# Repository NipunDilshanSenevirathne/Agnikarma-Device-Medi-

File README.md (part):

# Agni Karma Portable

**Five-preset thermal-applicator engineering project — P3R1, release 0.5.0.**

The intended product is a portable, battery-powered applicator with **50 / 100 / 150 / 200 / 250 degrees Celsius**, one interchangeable brass tip at a time, simple controls and a dedicated COOL button. This repository contains the current prototype software, electrical definition, routed controller carrier, mechanical source, engineering calculations and verification records.

**Current status:** the implemented design is a guarded modular bench prototype. It has not been manufactured, run on physical Pico boards or validated for patient use. The compact handheld housing, complete heated cartridge, qualified battery/charger and medical release are unfinished. The [build-completeness assessment](BUILD_COMPLETENESS.md) identifies those gaps. This README explains both the supplied implementation and the work needed to develop it further.

*AI-generated appearance illustration of the intended handheld product. Its housing is not the enclosure supplied for the current modular electronics. Rendered screens and wires are illustrations, not measured equipment or wiring instructions.*

## Contents

- [Project scope and current status](#project-scope-and-current-status)
- [Start here and document authority](#start-here-and-document-authority)
- [Functional requirements and user controls](#functional-requirements-and-user-controls)
- [System architecture and illustrations](#system-architecture-and-illustrations)
- [Repository layout and deliverables](#repository-layout-and-deliverables)
- [Parts list and procurement](#parts-list-and-procurement)
- [Power distribution and electrical boundaries](#power-distribution-and-electrical-boundaries)
- [Heater switching and relay circuit](#heater-switching-and-relay-circuit)
- [Controls and physical interlocks](#controls-and-physical-interlocks)
- [Temperature sensing and analog monitoring](#temperature-sensing-and-analog-monitoring)
- [Pico GPIO and physical header map](#pico-gpio-and-physical-header-map)
- [Routed PCB and fabrication files](#routed-pcb-and-fabrication-files)
- [Mechanical assembly and brass contact ends](#mechanical-assembly-and-brass-contact-ends)
- [Heater material and power calculations](#heater-material-and-power-calculations)
- [Battery charging and COOL behaviour](#battery-charging-and-cool-behaviour)
- [Computer setup and source verification](#computer-setup-and-source-verification)
- [Firmware deployment and commissioning records](#firmware-deployment-and-commissioning-records)
- [Operating sequence and software states](#operating-sequence-and-software-states)
- [Firmware limits protocol and failure boundaries](#firmware-limits-protocol-and-failure-boundaries)
- [Bench build sequence and inspection gates](#bench-build-sequence-and-inspection-gates)
- [Calibration and measurement records](#calibration-and-measurement-records)
- [Verification results and evidence limits](#verification-results-and-evidence-limits)
- [Troubleshooting and recovery](#troubleshooting-and-recovery)
- [Reproducing diagrams CAD and calculations](#reproducing-diagrams-cad-and-calculations)
- [Packaging GitHub and repository maintenance](#packaging-github-and-repository-maintenance)
- [Remaining engineering and medical release work](#remaining-engineering-and-medical-release-work)
- [Research sources and image provenance](#research-sources-and-image-provenance)
- [Appendix full system bill of materials](#appendix-full-system-bill-of-materials)
- [Appendix complete carrier connector table](#appendix-complete-carrier-connector-table)
- [Appendix all component terminal connections](#appendix-all-component-terminal-connections)

## Project scope and current status

The project has three distinct physical subjects: the **controller assembly**, the **external guarded power/sensor fixture**, and the **future interchangeable heated cartridge**. Understanding their boundaries is necessary before ordering or connecting parts.

| Subject | Supplied in this release | Development still required |
|---|---|---|
| Control software | Actual MicroPython applications for MAIN and SUPERVISOR, drivers, provisioning, host tests and simulation | Target execution, measured timing, hardware fault tests and software release validation |
| Electrical definition | Named components, values, full terminal connections, GPIO map and full-system schematic | Independent circuit/package review and physical electrical, thermal and fault measurements |
| Controller PCB | Routed 160 x 100 mm two-layer low-current carrier, matched schematic, local libraries and native reports | Independent CAM and purchased-part fit review, fabrication, assembly and continuity testing |
| Fabrication candidates | Six Gerber layers, separate plated/non-plated drills, maps and job file | Fabricator/assembler review and approval before ordering |
| Controller enclosure | Parametric 180 x 120 x 65 mm base, lid, mounts and harness cover; compiled meshes | Exact switch/display adapter fit, material, strength, wiring clearance and thermal testing |
| Brass contact ends | Five nominal shape models; T01/T02 electrical identity codes | Controlled material/process/tolerances and complete cartridge construction; T03–T05 software support |
| Heating cartridge | Functional supplier specification and resistance-wire calculations | Actual heater, ceramic, insulation, joints, dual sensors, lock, seals and supplier/finished-device testing |
| Portable power | Protected 2S architecture and monitoring circuits | Exact pack and matching charger, charging lockout, protection coordination, transport and heat-soak tests |
| Cooling | Physical relay-coil interruption and latched software cooling/inhibition | Measured cooldown and safe-handling criteria; active cooling if separately designed |
| Medical release | Risk, traceability, testing and handover documents | Intended use/market decisions, quality work, electrical/EMC, biological, reprocessing, usability and clinical/regulatory evidence |

The carrier is a **Pico breakout board**. It does not contain the external gate driver, power MOSFET, relay, branch resistors, sensor boards, ADC protection or battery charger. A populated carrier alone is not the complete controller circuit.

The AI illustrations, native CAD renders, calculation worksheets, host tests and physical-test forms have different evidentiary roles. A blank test form is a plan; a native rendering is a geometric view; a passing host test is a software result. None is a photograph or physical performance measurement.

## Start here and document authority

Use this README as the overview and detailed navigation guide. When making a connection, use the machine-readable terminal records and the applicable manufacturer drawing together.

| File | What it defines |
|---|---|
| [START_HERE.md](START_HERE.md) | Entry points and current project scope |
| [BUILD_GUIDE.md](BUILD_GUIDE.md) | Integrated prototype assembly sequence |
| [hardware/design.json](hardware/design.json) | Component references, terminal names, nets and notes |
| [hardware/BOM.csv](hardware/BOM.csv) | Full system component list, values and assembly notes |
| [hardware/component_connections.csv](hardware/component_connections.csv) | Every defined component terminal and its net |
| [hardware/pinmap.csv](hardware/pinmap.csv) | Pico GPIO number versus physical header pin |
| [hardware/net_schedule.csv](hardware/net_schedule.csv) | All terminals joined by each net name |
| [hardware/carrier_connectors.csv](hardware/carrier_connectors.csv) | Breakout connector pin versus Pico physical pin |
| [hardware/carrier_BOM.csv](hardware/carrier_BOM.csv) | Carrier board, sockets, headers, inlet and proposed fasteners |
| [hardware/procurement_checklist.csv](hardware/procurement_checklist.csv) | Purchased revisions, supplier decisions and evidence still needed |
| [AUDIT_REPORT.md](AUDIT_REPORT.md) | Corrected findings and current limitations |
| [BUILD_COMPLETENESS.md](BUILD_COMPLETENESS.md) | Remaining manufacturing and medical release gates |
| [docs/engineering-handover.md](docs/engineering-handover.md) | Instructions for an engineer, cartridge supplier and subsequent development |

In the connection records, identical non-NC net names mean electrical continuity. Names beginning with `NC_` identify terminals that remain unconnected. Do not join all NC terminals into a common circuit.

A module terminal such as `VIN`, `SDI`, `COM` or `COIL_A` is a functional terminal name. It does not automatically specify a numbered leg on the internal IC or relay package. Identify real package legs from the exact purchased part's manufacturer drawing. GPIO `GP21`, Pico physical pin `27` and carrier connector numbering are three different labels for related locations; do not interchange the numbers.

## Functional requirements and user controls

| Function | Current behaviour |
|---|---|
| Temperature selection | Five momentary buttons: **50, 100, 150, 200 and 250 C**; 300 C is not selectable |
| Startup | MAIN defaults to a 50 C target but remains locked with output inhibited |
| Tip connection | One positively locked, identified tip at a time; T01/T02 codes are recognized |
| ARM | A deliberate release followed by a new press, while HEAT is released, requests arming when checks are healthy |
| HEAT | Must be held to request heater energy; releasing it removes the output request |
| COOL | Interrupts the relay-coil supply through one physical switch pole and sends a logic request through the other |
| After COOL | Output stays inhibited; releasing COOL does not restart heating; valid conditions and a new ARM sequence are required |
| Setting change/fault | Disarms the controller; healthy readings alone do not restore heating |
| Docked condition | Physical coil interruption and logic inhibition |
| Tip removal/unlock | Opens the intended physical interlock and removes the logic permit |
| Display | MAIN shows state, selected setpoint, measured tip temperature, pack voltage and fault/status text |
| Temperature disagreement | Each controller checks its local sensor against the peer temperature |
| Communications loss | Stale UART or missing health pulses withdraw the software permit |

The five numbers are the available **setpoints**. The firmware also displays actual temperature and fault information. The illustrated five-value selection screen is not a literal capture of the running display.

Selection is shared through individual resistor branches to both boards. Firmware rejects a multiple-key condition. Press one selection button deliberately and allow both controllers to agree before arming; the operating procedure uses a press of at least 200 ms. This is a bench interaction procedure, not a clinical treatment protocol.

## System architecture and illustrations

MAIN reads its Pt1000 sensor, user inputs and monitoring circuits, runs the bounded temperature loop, updates the OLED and drives the PWM gate-driver input. SUPERVISOR reads a separate Pt1000 channel and its own monitoring/input branches, checks MAIN's status and controls the relay-coil transistor. MAIN also requires a healthy supervisor permit before delivering PWM.

The two controllers exchange CRC-protected UART frames and separate toggling health-pulse signals. A pulse is emitted after a completed acquisition/control/transmit iteration. Two boards improve monitoring options, but common software, runtime, supply, switches and ground remain common-cause failure paths requiring assessment.

```mermaid
flowchart LR
    P[Protected 2S pack or guarded bench source] --> F[F1 fused supply]
    F --> B[Pololu regulated 5 V logic supply]
    B --> M[MAIN Pico and local measurements]
    B --> S[SUPERVISOR Pico and local measurements]
    F --> K[K1 normally-open heater contact]
    K --> H[Guarded load or future insulated cartridge]
    H --> Q[Q1 PWM return switch]
    Q --> G[Power return]
    M --> D[TC4420 gate driver]
    D --> Q
    S --> C[Relay-coil transistor]
    I[Physical COOL / dock / lock chain] --> C
    M <--> S
```

The Mermaid drawing is functional. Use the terminal records and detailed drawings for actual contact/driver wiring.

*AI-generated bench-equipment illustration constrained to the specified equipment families. Individual leads and package geometry are approximate. The current native PCB and enclosure views below show supplied CAD; neither image proves assembly or wiring.*

## Repository layout and deliverables

```text
agni karma/
  README.md                    Detailed project guide
  START_HERE.md                Entry points
  BUILD_GUIDE.md               Integrated assembly sequence
  BUILD_COMPLETENESS.md        Open release gates
  AUDIT_REPORT.md              Source corrections and current findings
  SOURCE_MANIFEST.json         SHA-256 inventory of delivered source files
  firmware/
    app.py                     RP2040 hardware adapter and loop
    core.py                    Controllers, samples, fault logic and link protocol
    config.py                  Pins, five presets and provisional bench limits
    provision.py               Configuration validation
    provision.example.json     Disabled example commissioning record
    boot_main.py               MAIN role entry point
    boot_supervisor.py         SUPERVISOR role entry point
    drivers/                   MAX31865 and OLED drivers
  hardware/
    BOM.csv                    Full system BOM
    design.json                Machine-readable electrical definition
    component_connections.csv  Component-terminal-to-net data
    pinmap.csv                 GPIO and Pico physical header map
    net_schedule.csv           Connections grouped by net
    carrier_BOM.csv            Carrier assembly items
    carrier_connectors.csv     All four breakout headers
    procurement_checklist.csv  Supplier and qualification decisions
    calculations/              Power, drive, divider and resistance-wire worksheets
    kicad/                     Native projects, schematics, board and local libraries
    drawings/                  Native schematic/layer PDFs and exported netlist
    fabrication/P3R1/          Candidate Gerbers, drills, maps and instructions
  mechanical/
    bench_enclosure.scad       Controller base, lid, mounts and harness cover
    tips.scad                  Five nominal brass contact-end shapes
    assembly_parameters.json   Dimensions, locations and fit boundaries
    exports/                   Eight STL meshes and board-only STEP
  docs/
    images/                    AI illustrations, native renders and engineering drawings
    records/                   Actual check results and blank measurement forms
    ...                        Electrical, firmware, mechanical, test and handover guides
  tests/                       Host/integration/design/tooling checks
  tools/                       Verification, deployment, generation and packaging
  .github/                     CI workflow and issue/PR templates
```

`build/`, Python caches, local provisioning, editor caches and release ZIPs are generated/local material. They are excluded from the distributable source package. The cleaned project folder contains the current files and manifest; release archives are stored separately.

## Parts list and procurement

The full system contains **78 defined component references**. A reference is a design item, not proof that an exact supplier SKU, purchased revision or final cartridge has been qualified. Full values and notes appear in the BOM appendix below.

| Subsystem | Defined part or specification | Procurement consideration |
|---|---|---|
| MAIN/SUPERVISOR | Two original Raspberry Pi Pico RP2040 boards | Confirm purchased revision, header orientation and target runtime |
| RTD interfaces | Two Adafruit **3648** Pt1000 MAX31865 breakouts | 4.3 kohm reference version; a Pt100 board is not equivalent |
| Temperature elements | Two separate four-wire Pt1000 assemblies, alpha 0.00385 family | Actual package, leads, retention and insulation remain supplier work |
| Logic regulator | Pololu **2858 / D24V22F5** | Regulated 5 V to VSYS; review input/thermal conditions |
| Gate driver | **TC4420CPA**, non-inverting, PDIP-8 | TC4429 inverting variant is not a direct substitute |
| PWM switch | Infineon **IRLZ44NPBF**, TO-220 | Verify gate drive, dissipation, mounting and live drain tab |
| Heater relay | Omron **G5LE-1-DC5** | Normally-open contact; not a certified redundant safety relay |
| Relay transistor | onsemi **PN2222ABU**, TO-92 | Exact package pinout matters; similarly named variants can differ |
| Flyback diode | **1N4007** | Polarity across coil; suppression affects release time |
| Display | Adafruit **326**, STEMMA QT auto-reset SSD1306 revision | I2C mode/address and actual adapter fit must be checked |
| Commissioning load | **2.2 ohm, at least 100 W chassis resistor**, on its specified heat sink | Continuous rating depends on mounting/heat sink; not a medical tip |
| Initial fuse proposal | **5 A**, with suitable DC-rated holder | Final interrupt rating and curve/wire/pack coordination remain open |
| Controls | Five NO preset buttons, ARM, HEAT, DPDT COOL, two-pole dock/lock switches | Exact parts/contact ratings and fit need selection |
| Portable source | Protected **2S** battery pack and matched charger | Exact models, charge lockout and system qualification are open |

Carrier-only components and proposed fasteners are separately defined:

| Reference | Quantity | Specification | Use or review |
|---|---|---|---|
| `PCB_CARRIER` | 1 | AGNI P3R1; 160 x 100 mm; 2-layer FR4; nominal 1.6 mm; 35 um copper; mask both sides; top silkscreen | Fabrication candidate only; independent CAM and physical footprint review before order |
| `A1/A2 sockets` | 4 | 1x20 female socket strip; 2.54 mm pitch; 0.64 mm square-pin compatible; straight through-hole; 1.0 mm PCB drill | Two strips per Pico; choose matched stack height; verify orientation and engagement |
| `J1/J2/J3/J4` | 4 | 1x20 straight male header; 2.54 mm pitch; 0.64 mm square posts; 1.0 mm drill | Low-current external breakouts; external 1k branches and all other circuits still required |
| `J5` | 1 | Phoenix Contact 1715721 MKDS 1.5/2-5.08; 2-position; 5.08 mm pitch; 1.3 mm drill | Pin 1 GND; pin 2 regulated 5 V only; confirm actual footprint and torque against current supplier drawing |
| `Carrier screws` | 4 | M3 x 6 pan head; insulating washers as needed | Fit model pilot posts; check protrusion and engagement |
| `Lid screws` | 4 | M3 x 10 pan head | Fit model pilot posts; qualify repeated use |
| `Clamp screws` | 2 | M3 x 10 pan head with washers | Check cable retention; insulating grommet required |

Do not add carrier sockets/headers to the full system twice when preparing a purchase order. The two Pico modules are already system items; socket strips support those modules. Module-internal ICs/passives remain manufacturer-controlled components rather than a guessed replacement circuit in this repository.

Record supplier, exact part revision, evidence identifier and substitutions in [procurement_checklist.csv](hardware/procurement_checklist.csv). Wire gauge, high-current connector, final fuse, battery, charger, precise sensor package, switches and complete cartridge must be resolved before treating procurement as finished. No current prices, supplier quotations or total product cost are established here.

## Power distribution and electrical boundaries

The nominal heating branch and regulated logic branch share the defined return but have different current paths:

```text
Source positive -> F1 -> PACK_FUSED -> K1 COM
K1 NO -> HEAT_PLUS -> guarded load/heater -> HEAT_MINUS -> Q1 drain
Q1 source -> dedicated power return -> source negative

PACK_FUSED -> Pololu VIN
Pololu VOUT 5 V -> carrier J5 pin 2 -> Pico VSYS, driver and coil circuit
Power/logic GND -> carrier J5 pin 1 and the defined circuit return

MAIN 3V3_OUT -> MAIN RTD interface and MAIN measurement pull-ups
SUP  3V3_OUT -> SUP  RTD interface and SUP  measurement pull-ups
```

The two Pico **3V3_OUT** pins are separate regulator outputs. Keep `3V3_MAIN` and `3V3_SUP` separate. `5V` is regulated logic power; `PACK_FUSED` is the fused battery/bench input. Never substitute one for the other at the Pico, GPIO, ADC or carrier inlet.

Do not route heater current through the carrier headers, sensor-module ground leads or a solderless breadboard. Use mechanically retained, appropriately rated power terminals/harnesses and a controlled return arrangement. Review layout, conductor/insulation ratings, loop area, supply transients and grounding against measured currents. A nominal fuse value alone does not settle these questions.

Keep USB disconnected during powered heater tests unless the combined USB/bench/battery supply and grounding arrangement has been reviewed. USB can introduce another return or source path; it is not medical isolation. The passive carrier has no reverse-polarity protection.

Start commissioning with an instrumented current-limited bench supply and disconnected heater. A portable pack is a later integration step; it is not automatically qualified by using a protected cell assembly.

## Heater switching and relay circuit

[Detailed terminal wiring PNG](docs/images/terminal-wiring.png) · [editable terminal wiring SVG](docs/images/terminal-wiring.svg) · [full-system schematic PDF](hardware/drawings/module-system-schematic.pdf)

### Main PWM path

MAIN `GP21` drives `PWM_INPUT`. U1 is the non-inverting TC4420CPA powered from regulated 5 V. Its duplicated output pins join `DRIVE`; the 10 ohm resistor connects DRIVE to Q1 gate. Q1 switches the heater return at the configured 1 kHz PWM frequency.

| Part / terminal | Defined connection |
|---|---|
| U1 pins 1 and 8 | Regulated `5V` |
| U1 pin 2 | `PWM_INPUT` from MAIN GP21 |
| U1 pin 3 | Unconnected (`NC_U1_3`) |
| U1 pins 4 and 5 | `GND` |
| U1 pins 6 and 7 | Joined as `DRIVE` |
| R1, 10 ohm | DRIVE to Q1 gate (`MOS_GATE`) |
| R2, 100k | Q1 gate to source/GND |
| R3, 100k | Driver input to GND |
| C1, 100 nF / 25 V X7R | Driver 5 V bypass to GND |
| C2, 1 uF / 25 V X7R | Driver 5 V bypass to GND |
| C3, 100 uF / 16 V low ESR | Positive to 5 V, negative to GND |
| Q1 pin 1 | Gate |
| Q1 pin 2 and tab | Drain / `HEAT_MINUS` |
| Q1 pin 3 | Source / power GND |

The package/duplicate-pin reference is the [Microchip TC4420/TC4429 datasheet](https://ww1.microchip.com/downloads/en/DeviceDoc/21419D.pdf). Keep bypass loops short at the driver. The Q1 tab is electrically live drain, so a heat sink, screw or chassis contact must not create an unintended connection. Actual switching waveform, gate behaviour, losses and surface temperatures must be measured.

### Supervisor relay path

K1 COM receives `PACK_FUSED`; its normally-open contact supplies `HEAT_PLUS`. Its unused normally-closed contact stays unconnected. The coil circuit is separate from those power contacts.

```text
5V -> COOL pole A COM/NC -> dock pole A COM/NC
   -> locked-tip pole A COM/NO -> K1 COIL_A
K1 COIL_B -> Q2 collector
Q2 emitter -> GND
SUPERVISOR GP21 -> R4 330 ohm -> Q2 base
Q2 base -> R5 100k -> GND
D1 cathode -> COIL_A; D1 anode -> COIL_B
```

For the specified PN2222ABU record, terminals are **1 emitter, 2 base, 3 collector**. Verify the actual manufacturer's drawing and package before soldering. The repository uses Omron coil/COM/NO functional names; identify the real relay legs from its exact package drawing rather than assuming those names are pin numbers.

Opening COOL, docking or unlocking/removing the cartridge interrupts the intended coil chain. A welded relay contact or shorted MOSFET is a separate fault scenario; the circuit has not been certified to tolerate those faults. A flyback diode protects the coil switch but changes release timing. Measure relay release and resulting energy instead of treating the software timeout as the physical stop time.

## Controls and physical interlocks

Each shared logic switch connects a bus to GND when active. Each controller reaches that bus through its **own 1k branch resistor**, using its own internal input pull-up. This shares the switch action without joining the two 3V3 regulator outputs.

For an ordinary preset, the path is `MAIN GPIO -> MAIN 1k -> switch bus`, `SUP GPIO -> SUP 1k -> same bus`, then the NO switch to GND. ARM and HEAT use the same branching principle. The full terminal appendix contains their actual reference/net names.

| Interlock | Physical pole A | Logic pole B | Meaning when actuated |
|---|---|---|---|
| COOL | COM to NC is in the coil supply path | COM GND to NO `COOL_LOGIC` | Coil supply opens and both controllers read COOL active |
| Dock | COM to NC is in the coil supply path | COM GND to NO `DOCK_LOGIC` | Coil supply opens and both controllers read docked |
| Tip lock | COM to NO is in the coil supply path | COM GND to NO `TIP_PRESENT` | Positive locking must close the intended contacts; unlocked state inhibits |

Pole A and pole B must be electrically separate. Do not connect the 5 V coil chain to a GPIO logic bus. A single-pole replacement for the specified DPDT COOL function is insufficient. Confirm physical actuation/sequence and contact ratings against coil current and the real mechanism.

The logic inputs are active-low. The tip-present contact closes only when a cartridge is positively locked; an operator holding a loose part near a connector is not an equivalent mechanical condition. Broken, stuck, shorted and bouncing wires/switches still require controlled physical fault tests.

## Temperature sensing and analog monitoring

[Editable sensor-wiring SVG](docs/images/sensor-wiring.svg)

### Two separate Pt1000 channels

Each controller has its own Adafruit 3648 MAX31865 interface, its own Pt1000 element and its own 3V3 regulator output. The configured reference is nominally **4300 ohm**, and the nominal RTD resistance is **1000 ohm at 0 C**. The firmware uses continuous conversion, four-wire configuration and 50 Hz rejection.

| Interface terminal | Controller / sensor connection |
|---|---|
| VIN | That controller's own 3V3 output |
| GND | Defined GND |
| SCK | Local GP6 |
| SDI | Local GP7 MOSI |
| SDO | Local GP4 MISO |
| CS | Local GP5 |
| F+ | Force lead at sensor element end A |
| RTD+ | Separate sense lead at the same element end A |
| RTD- | Sense lead at element end B |
| F- | Separate force lead at the same element end B |
| 3Vo | Unused output; leave unconnected |

Identify element-end pairs from the actual sensor documentation and measurements, not wire colour alone. A two-wire element with arbitrary added wires is not automatically the qualified four-wire cartridge assembly specified here. Keep the supplied four-wire jumper arrangement appropriate to the actual module; verify with the [manufacturer terminal guide](https://learn.adafruit.com/adafruit-max31865-rtd-pt100-amplifier/pinouts).

SPI0 is configured at **500 kHz, polarity 0, phase 1**. MAIN and SUPERVISOR do not share the same SPI sensor module. Sensor-to-working-face gradients, response lag, attachment integrity and electrical insulation remain cartridge verification tasks.

### Pack voltage

Each controller has its own chain: `PACK_FUSED -> 100k -> divider node -> 39k -> GND`. A separate 1k resistor connects the divider node to that controller's GP26 ADC. The ADC node has 10 nF to GND, an upper BAT54 clamp with anode at ADC/cathode at its own 3V3 rail, and a lower BAT54 clamp with anode at GND/cathode at ADC.

The firmware's ideal conversion is:

```text
pack_v = adc_u16 / 65535 * 3.3 * (139 / 39) * battery_scale
```

At an 8.5 V input, the ideal divider output is about 2.385 V; the worksheet's 1% worst-case resistor mismatch gives about 2.419 V. Actual ADC/reference behaviour, filtering, clamp leakage and unpowered backfeeding need measurement. Do not connect pack voltage directly to a Pico ADC or treat the clamps as complete pack protection.

### Pack temperature

Each controller has a 10k pull-up from its own 3V3 rail to GP27 and an insulated **10k at 25 C, B3950 NTC** from that node to GND. The software converts the divider ratio using the configured beta approximation. The two sensors need appropriate thermal attachment to the pack and independent wiring; electrical readings alone do not prove good thermal coupling.

### Tip identity

Each controller has a 10k pull-up from its own 3V3 rail to GP28 and its own cartridge code resistor to GND:

| Tip | Code resistor per channel | Nominal ADC ratio | Current firmware |
|---|---|---|---|
| T01 | 10k | 0.5000 | Recognized |
| T02 | 16k | 0.6154 | Recognized |
| T03/T04/T05 | No released code | No supported ratio | Not supported |

The ratio acceptance tolerance is nominally +/-0.025. The two channels use separate pull-up/code circuits. A resistor code does not establish authenticity, sterility or a valid calibration. The current UART frame does not carry the tip ID for a separate peer-ID comparison; each controller checks its own recognized code. Additional identity/calibration features require a reviewed implementation.

### Display

Use the specified Adafruit 326 **STEMMA QT auto-reset** revision. The defined wiring is VIN to `3V3_MAIN`, GND to GND, SDA to MAIN GP2 and SCL to MAIN GP3. MAIN uses I2C1 at 400 kHz. The older reset-dependent display revision needs a changed circuit/firmware and is not covered by this wiring.

Provision the actual address as decimal **60 (0x3C)** or **61 (0x3D)**. A missing display prevents normal MAIN provisioning. The display update interval is at least 250 ms in the application; displayed state is not an independent temperature measurement or clinical READY signal.

## Pico GPIO and physical header map

Both controllers use the same GPIO roles except that the display belongs to MAIN and the GP21 outputs perform different functions. The table is generated from [pinmap.csv](hardware/pinmap.csv); its GPIO column is not a connector-pin number.

| GPIO | Pico physical pin | MAIN net | SUPERVISOR net |
|---|---|---|---|
| `GP0` | 1 | `MAIN_TX` | `SUP_TX` |
| `GP1` | 2 | `MAIN_RX` | `SUP_RX` |
| `GP2` | 4 | `OLED_SDA` | `Unassigned` |
| `GP3` | 5 | `OLED_SCL` | `Unassigned` |
| `GP4` | 6 | `MAIN_MISO` | `SUP_MISO` |
| `GP5` | 7 | `MAIN_CS` | `SUP_CS` |
| `GP6` | 9 | `MAIN_SCK` | `SUP_SCK` |
| `GP7` | 10 | `MAIN_MOSI` | `SUP_MOSI` |
| `GP8` | 11 | `MAIN_KEY_50` | `SUP_KEY_50` |
| `GP9` | 12 | `MAIN_KEY_100` | `SUP_KEY_100` |
| `GP10` | 14 | `MAIN_KEY_150` | `SUP_KEY_150` |
| `GP11` | 15 | `MAIN_KEY_200` | `SUP_KEY_200` |
| `GP12` | 16 | `MAIN_KEY_250` | `SUP_KEY_250` |
| `GP14` | 19 | `MAIN_KEY_COOL` | `SUP_KEY_COOL` |
| `GP15` | 20 | `MAIN_KEY_HEAT` | `SUP_KEY_HEAT` |
| `GP16` | 21 | `MAIN_KEY_ARM` | `SUP_KEY_ARM` |
| `GP17` | 22 | `MAIN_KEY_DOCK` | `SUP_KEY_DOCK` |
| `GP18` | 24 | `MAIN_KEY_TIP` | `SUP_KEY_TIP` |
| `GP19` | 25 | `MAIN_PULSE_IN` | `SUP_PULSE_IN` |
| `GP20` | 26 | `MAIN_PULSE_OUT` | `SUP_PULSE_OUT` |
| `GP21` | 27 | `PWM_INPUT` | `SUP_RELAY_OUTPUT` |
| `GP26` | 31 | `MAIN_PACK_ADC` | `SUP_PACK_ADC` |
| `GP27` | 32 | `MAIN_NTC_ADC` | `SUP_NTC_ADC` |
| `GP28` | 34 | `MAIN_ID_ADC` | `SUP_ID_ADC` |

Additional supply and ground connections on each Pico are:

| Physical Pico pin | Function in this assembly |
|---|---|
| 39 | VSYS from regulated 5 V |
| 36 | That Pico's own 3V3_OUT; keep the two boards' outputs separate |
| 3, 8, 13, 18, 23, 28, 33, 38 | GND on the carrier |
| 17 / GP13 | Unused in the five-preset design |
| 29 / GP22 | Reserved/spare in configuration; not assigned to an implemented external function |
| 30 / RUN | Unconnected on the carrier |
| 35 / ADC_VREF | Unconnected external breakout pad |
| 37 / 3V3_EN | Unconnected on the carrier |
| 40 / VBUS | Unconnected on the carrier; not a battery-power inlet |

SUPERVISOR GP2/GP3 have no display assignment in the supplied pin schedule. Unused Pico positions and corresponding breakout pads are isolated from one another rather than routed as arbitrary extra signals.

UART0 runs at **115200 baud**. MAIN TX goes through `R_LINK_M` 1k to SUP RX; SUP TX goes through `R_LINK_S` 1k to MAIN RX. MAIN GP20 health output goes through `R_PULSE_M` 1k to SUP GP19. SUP GP20 goes through `R_PULSE_S` 1k to MAIN GP19. The peer pulse inputs use pull-downs; the normal local outputs begin low.

## Routed PCB and fabrication files

*These are KiCad 10.0.8 raytraces of the actual supplied bare-board geometry. Component bodies are not fitted in these renders. They are neither AI board concepts nor photographs of manufactured hardware.*

### Board geometry and connector orientation

| Feature | Current definition |
|---|---|
| Board size | 160 x 100 mm |
| Board thickness | Nominal 1.6 mm |
| Copper layers | Two; proposed nominal 35 um copper, subject to fabricator agreement |
| Signal tracks | 0.35 mm |
| Logic supply/ground tracks | 0.60 mm; no heater-current capacity claim |
| Declared clearance | 0.20 mm |
| Declared copper-to-edge minimum | 0.50 mm |
| Pico row pitch | 2.54 mm longitudinal, 17.78 mm between rows |
| MAIN left header row | X=35 mm, top pad Y=20 mm |
| SUP left header row | X=105 mm, top pad Y=20 mm |
| Header drills | 1.0 mm |
| J5 terminal drills | 1.3 mm |
| Mounting holes | Four non-plated 3.2 mm holes at (5,5), (155,5), (5,95), (155,95) mm |

Coordinates are measured from the board's upper-left corner in the supplied CAD convention. The mounting pattern is also recorded in [assembly_parameters.json](mechanical/assembly_parameters.json).

J1 is MAIN's left breakout, J2 its right breakout, J3 SUP's left breakout and J4 its right breakout. **Each breakout strip is numbered from top to bottom 1–20.** On J1/J3, connector pin `j` corresponds to Pico physical pin `j`. On J2/J4, connector pin `j` corresponds to Pico physical pin `41-j`. Thus right breakout pin 1 corresponds to Pico physical pin 40; it is an isolated unused position, not MAIN/SUP TX.

J5 is a two-position **regulated logic-power inlet**: **pin 1 GND, pin 2 regulated 5 V**. The selected terminal is Phoenix Contact 1715721, MKDS 1.5/2-5.08. Verify the real purchased terminal and footprint before ordering. Never apply `PACK_FUSED` or heater current to J5.

The complete four-header map appears in the carrier appendix below. The native netlist tests compare it with the separate Pico pin schedule, including right-side reversal and isolated unused pads.

### Source and drawing files

| Item | File |
|---|---|
| Carrier project | [agni-controller-carrier.kicad_pro](hardware/kicad/agni-controller-carrier.kicad_pro) |
| Carrier schematic | [agni-controller-carrier.kicad_sch](hardware/kicad/agni-controller-carrier.kicad_sch) |
| Routed carrier board | [agni-controller-carrier.kicad_pcb](hardware/kicad/agni-controller-carrier.kicad_pcb) |
| Full-system schematic project | [agni-module-system.kicad_pro](hardware/kicad/agni-module-system.kicad_pro) |
| Full-system module/terminal schematic | [agni-module-system.kicad_sch](hardware/kicad/agni-module-system.kicad_sch) |
| Project symbol library | [AGNI.kicad_sym](hardware/kicad/AGNI.kicad_sym) |
| Library tables | [sym-lib-table](hardware/kicad/sym-lib-table), [fp-lib-table](hardware/kicad/fp-lib-table) |
| Carrier schematic PDF | [carrier-schematic.pdf](hardware/drawings/carrier-schematic.pdf) |
| Full-system schematic PDF | [module-system-schematic.pdf](hardware/drawings/module-system-schematic.pdf) |
| Copper/silk/outline PDF | [carrier-layers.pdf](hardware/drawings/carrier-layers.pdf) |
| Native layer plots | [top SVG](docs/images/carrier-top.svg), [bottom SVG](docs/images/carrier-bottom.svg), [combined routing SVG](docs/images/carrier-routing.svg) |
| Exported electrical netlist | [carrier-netlist.xml](hardware/drawings/carrier-netlist.xml) |
| Board-only mechanical model | [carrier-board-only.step](mechanical/exports/carrier-board-only.step) |

The `hardware/kicad/AGNI.pretty/` directory contains the project-local footprints. Keep it and both library tables with the project so references remain portable.

Both schematics use embedded/project-local **generic passive terminal symbols**. Native ERC verifies the represented connectivity and structure; it does not check real internal IC power/signal directions. The full-system schematic covers external circuits that are absent from the carrier PCB. A clean carrier DRC is not a safety test of the complete heater circuit.

### Candidate CAM outputs

Read [fabrication/P3R1/README.md](hardware/fabrication/P3R1/README.md) before sending files to a fabricator.

| Output | Filename within `hardware/fabrication/P3R1/` |
|---|---|
| Front copper | `agni-controller-carrier-F_Cu.gtl` |
| Back copper | `agni-controller-carrier-B_Cu.gbl` |
| Front silkscreen | `agni-controller-carrier-f_silkscreen.gto` |
| Front solder mask | `agni-controller-carrier-F_Mask.gts` |
| Back solder mask | `agni-controller-carrier-B_Mask.gbs` |
| Closed outline | `agni-controller-carrier-Edge_Cuts.gm1` |
| Plated drills | `agni-controller-carrier-PTH.drl` — 160 holes at 1.0 mm, two at 1.3 mm |
| Non-plated drills | `agni-controller-carrier-NPTH.drl` — four holes at 3.2 mm |
| Drill maps | Corresponding `PTH-drl_map.svg` and `NPTH-drl_map.svg` |
| Job file | `agni-controller-carrier-job.gbrjob` |
| Drill summary | `drill-report.txt` |

Copper, mask, outline and drill files must be reviewed together, at the same scale and origin, in a CAM viewer. Confirm stack, drill plating, annular rings, mask polarity/openings, silk clearance, terminal footprint and 1:1 fit with actual parts. Do not scale a viewing image for manufacturing or independently mirror/change one layer's origin. Fabrication files remain candidates pending independent review and physical checks.

## Mechanical assembly and brass contact ends

### Controller housing

The supplied enclosure is for the carrier and controls. It is **180 x 120 x 65 mm**, with 3 mm wall/floor thickness and a 3 mm removable lid. It includes four carrier standoffs, four lid posts, preset/control bores, an OLED window/adapter rails and a split harness-cover model.

The carrier origin in the housing is **(10,10,9) mm**. Its four board mounting holes translate to housing coordinates **(15,15), (165,15), (15,105), (165,105) mm**. Lid screw positions are **(7,7), (173,7), (7,113), (173,113) mm**. Coordinate arithmetic and exported geometry were checked; actual fit and strength have not been measured.

| Interface | Defined geometry / proposed item | Fit work still needed |
|---|---|---|
| Five presets | Five 8.2 mm bores | Select actual switches and verify bodies, nuts and wiring clearance |
| ARM/HEAT/COOL | Three 12.2 mm bores | Check actual contact arrangement, ratings and body depth |
| OLED | 30 x 18 mm window with adjustable adapter rails | Measure purchased Adafruit 326 revision and produce its matching adapter |
| Harness exit | 24 mm open slot with split cover | Suitable insulating grommet, routing, retention and pull tests |
| Carrier attachment | Four proposed M3 x 6 pan-head screws into prototype pilot posts | Check engagement, protrusion, material and repeated assembly |
| Lid | Four proposed M3 x 10 pan-head screws | Verify thread engagement and strength |
| Harness cover | Two proposed M3 x 10 screws with washers | Verify clamp/grommet fit and cable retention |

The heater, brass end, pack, charger, relay, power switch stage and RTD breakout boards stay on the external guarded fixture. They are not positioned inside this controller housing. A complete portable handpiece requires a new integrated mechanical/electrical layout around qualified parts.

The printed-shell model has no established heat, flame, impact, ingress, reprocessing or medical-material rating. Pilot posts and proposed screws are fit-trial features, not a released fastening process. The exported lid is translated so its lowest rail surface is at Z=0; orient it appropriately for manufacturing, accounting for the inward-facing rails and supports.

### Brass contact-end shapes

| ID | Nominal working-end shape | Approximate CAD envelope | Electrical support |
|---|---|---|---|
| T01 | 2 mm rounded end | 5 mm stem, taper and small neck; about 22 mm overall | 10k identity code per channel |
| T02 | 4 mm rounded dome | 5 mm stem, taper and neck; about 23 mm overall | 16k identity code per channel |
| T03 | 6 mm disc | Disc 2 mm thick on stem; 21 mm overall | Not enabled |
| T04 | 6 x 2 mm line envelope | Blended rounded plate on stem; 21 mm overall | Not enabled |
| T05 | 3 mm angled rounded end | Neck at 30 degrees; about 23.56 mm high | Not enabled |

These are nominal **contact-end shape studies**. They do not specify lesion size, contact force/time, indication or clinical dose. They have no released heater/sensor cavities, cartridge lock, seals, material tolerances or surface-finish instructions. Machining only these shapes does not produce a complete heated tip.

The candidate brass family discussed in the cartridge specification is **CuZn30**, subject to material/process and finished-device evaluation. It is not a material approval. Do not treat leaded free-machining C36000 as an equivalent. Certificates and finished-part evaluation must address impurities, machining residues, corrosion/oxidation, joining materials and repeated reprocessing. Plating would add separate adhesion, wear and chemical risks.

### Mechanical source and exports

| File | Role |
|---|---|
| [bench_enclosure.scad](mechanical/bench_enclosure.scad) | Editable controller base/lid/cover model |
| [tips.scad](mechanical/tips.scad) | Editable contact-end family; `tip_id=1..5` selects a single shape |
| [assembly_parameters.json](mechanical/assembly_parameters.json) | Dimensions, screw proposals and scope |
| [controller-base.stl](mechanical/exports/controller-base.stl) | Native closed base mesh |
| [controller-lid.stl](mechanical/exports/controller-lid.stl) | Native closed lid mesh |
| [harness-clamp.stl](mechanical/exports/harness-clamp.stl) | Native closed cover/clamp mesh |
| [T01 STL](mechanical/exports/T01-shape.stl), [T02 STL](mechanical/exports/T02-shape.stl), [T03 STL](mechanical/exports/T03-shape.stl), [T04 STL](mechanical/exports/T04-shape.stl), [T05 STL](mechanical/exports/T05-shape.stl) | Native closed contact-end meshes |
| [carrier-board-only.step](mechanical/exports/carrier-board-only.step) | Board/hole model; no fitted component-height models |
| [mechanical-checks.json](docs/records/mechanical-checks.json) | Tool version, mesh bounds/triangles, closed-edge checks and hashes |

The eight STL meshes passed native OpenSCAD compilation and closed-edge incidence checks. A closed mesh proves neither printable tolerances nor strength, fit, heat resistance or sterilization suitability. See [mechanical.md](docs/mechanical.md) for the detailed boundaries.

## Heater material and power calculations

The actual electrical commissioning load is `H_TEST`, the guarded 2.2 ohm chassis resistor on its specified heat sink. A future heated cartridge needs a reviewed insulated heater/sensor construction. It is not supplied as a proven winding assembly in this release.

For a nominal resistance `R` at supply voltage `V`:

```text
On-current             I_on = V / R
Full-on electrical power  P = V*V / R
Average PWM power      P_avg = duty * V*V / R
Firmware command cap   duty <= min(0.50, 30 * 2.2 / (V*V))
```

For 2.2 ohm nominal resistance:

| Input V | Full on-current A | Full on-power W | Command duty cap | Nominal average W at cap |
|---|---|---|---|---|
| 6.2 | 2.818 | 17.473 | 50.0% | 8.736 |
| 7.4 | 3.364 | 24.891 | 50.0% | 12.445 |
| 8.4 | 3.818 | 32.073 | 50.0% | 16.036 |
| 8.5 | 3.864 | 32.841 | 50.0% | 16.421 |

These are electrical calculations, not measured cartridge temperatures or heat-up times. Switching parts and conductors see **full on-current** during each PWM pulse. At 8.4 V the nominal full-on values are about 3.82 A and 32.07 W, even though a 50% command produces about 16.04 W average.

The firmware uses nominal resistance rather than measured current. A -10% resistance deviation increases actual current/power by about 11.1% for a given voltage/duty. A partial short can therefore defeat the assumed relationship; the voltage-based command limit does not replace fault protection or current measurement. The nominal 30 W software cap is also distinct from the initial 50% duty restriction.

The proposed resistance-wire family is **NiCr 80/20**, for example **Kanthal Nikrothal 80**. The worksheet uses its stated 20 C resistivity of **1.09 ohm mm²/m**, from the [manufacturer material data](https://www.kanthal.com/products/datasheets/material-datasheets/wire/resistance-heating-wire-and-resistance-wire/nikrothal-80/):

```text
Wire cross-section A = pi * diameter_mm^2 / 4
Cold wire length_m  = target_resistance_ohm * A / resistivity
```

| Wire diameter mm | Calculated cold length for 2.2 ohm, mm | Calculated full-on wire-surface load at 8.4 V, W/cm2 |
|---|---|---|
| 0.15 | 35.667 | 190.821 |
| 0.2 | 63.408 | 80.503 |
| 0.25 | 99.075 | 41.217 |
| 0.3 | 142.669 | 23.853 |
| 0.35 | 194.188 | 15.021 |
| 0.4 | 253.633 | 10.063 |

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
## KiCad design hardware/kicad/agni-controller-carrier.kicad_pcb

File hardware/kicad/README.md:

# Native KiCad projects, P3R1

Open `agni-controller-carrier.kicad_pro` for the routed passive carrier and matched schematic. Open `agni-module-system.kicad_pro` for the complete external module/terminal wiring schematic. The project-local AGNI libraries are included; preserve the directory structure and library-table files.

KiCad 10.0.8 ran ERC on both schematics and carrier DRC with schematic parity: all reported finding counts are zero. Exact reports, commands, limitations and input hashes are in [native-cad-checks.json](../../docs/records/native-cad-checks.json).

The carrier is 160 x 100 mm and carries only regulated logic supply and GPIO breakout wiring. External branch resistors and heater/sensor/power circuits are not silently integrated onto this PCB. Generic passive terminal symbols do not provide full component-direction ERC.

Use the [PCB guide](../../docs/pcb.md), [connector schedule](../carrier_connectors.csv), [carrier BOM](../carrier_BOM.csv) and [fabrication review instructions](../fabrication/P3R1/README.md). CAM files are engineering candidates pending independent review and physical fit/continuity tests, not a medical manufacturing release.

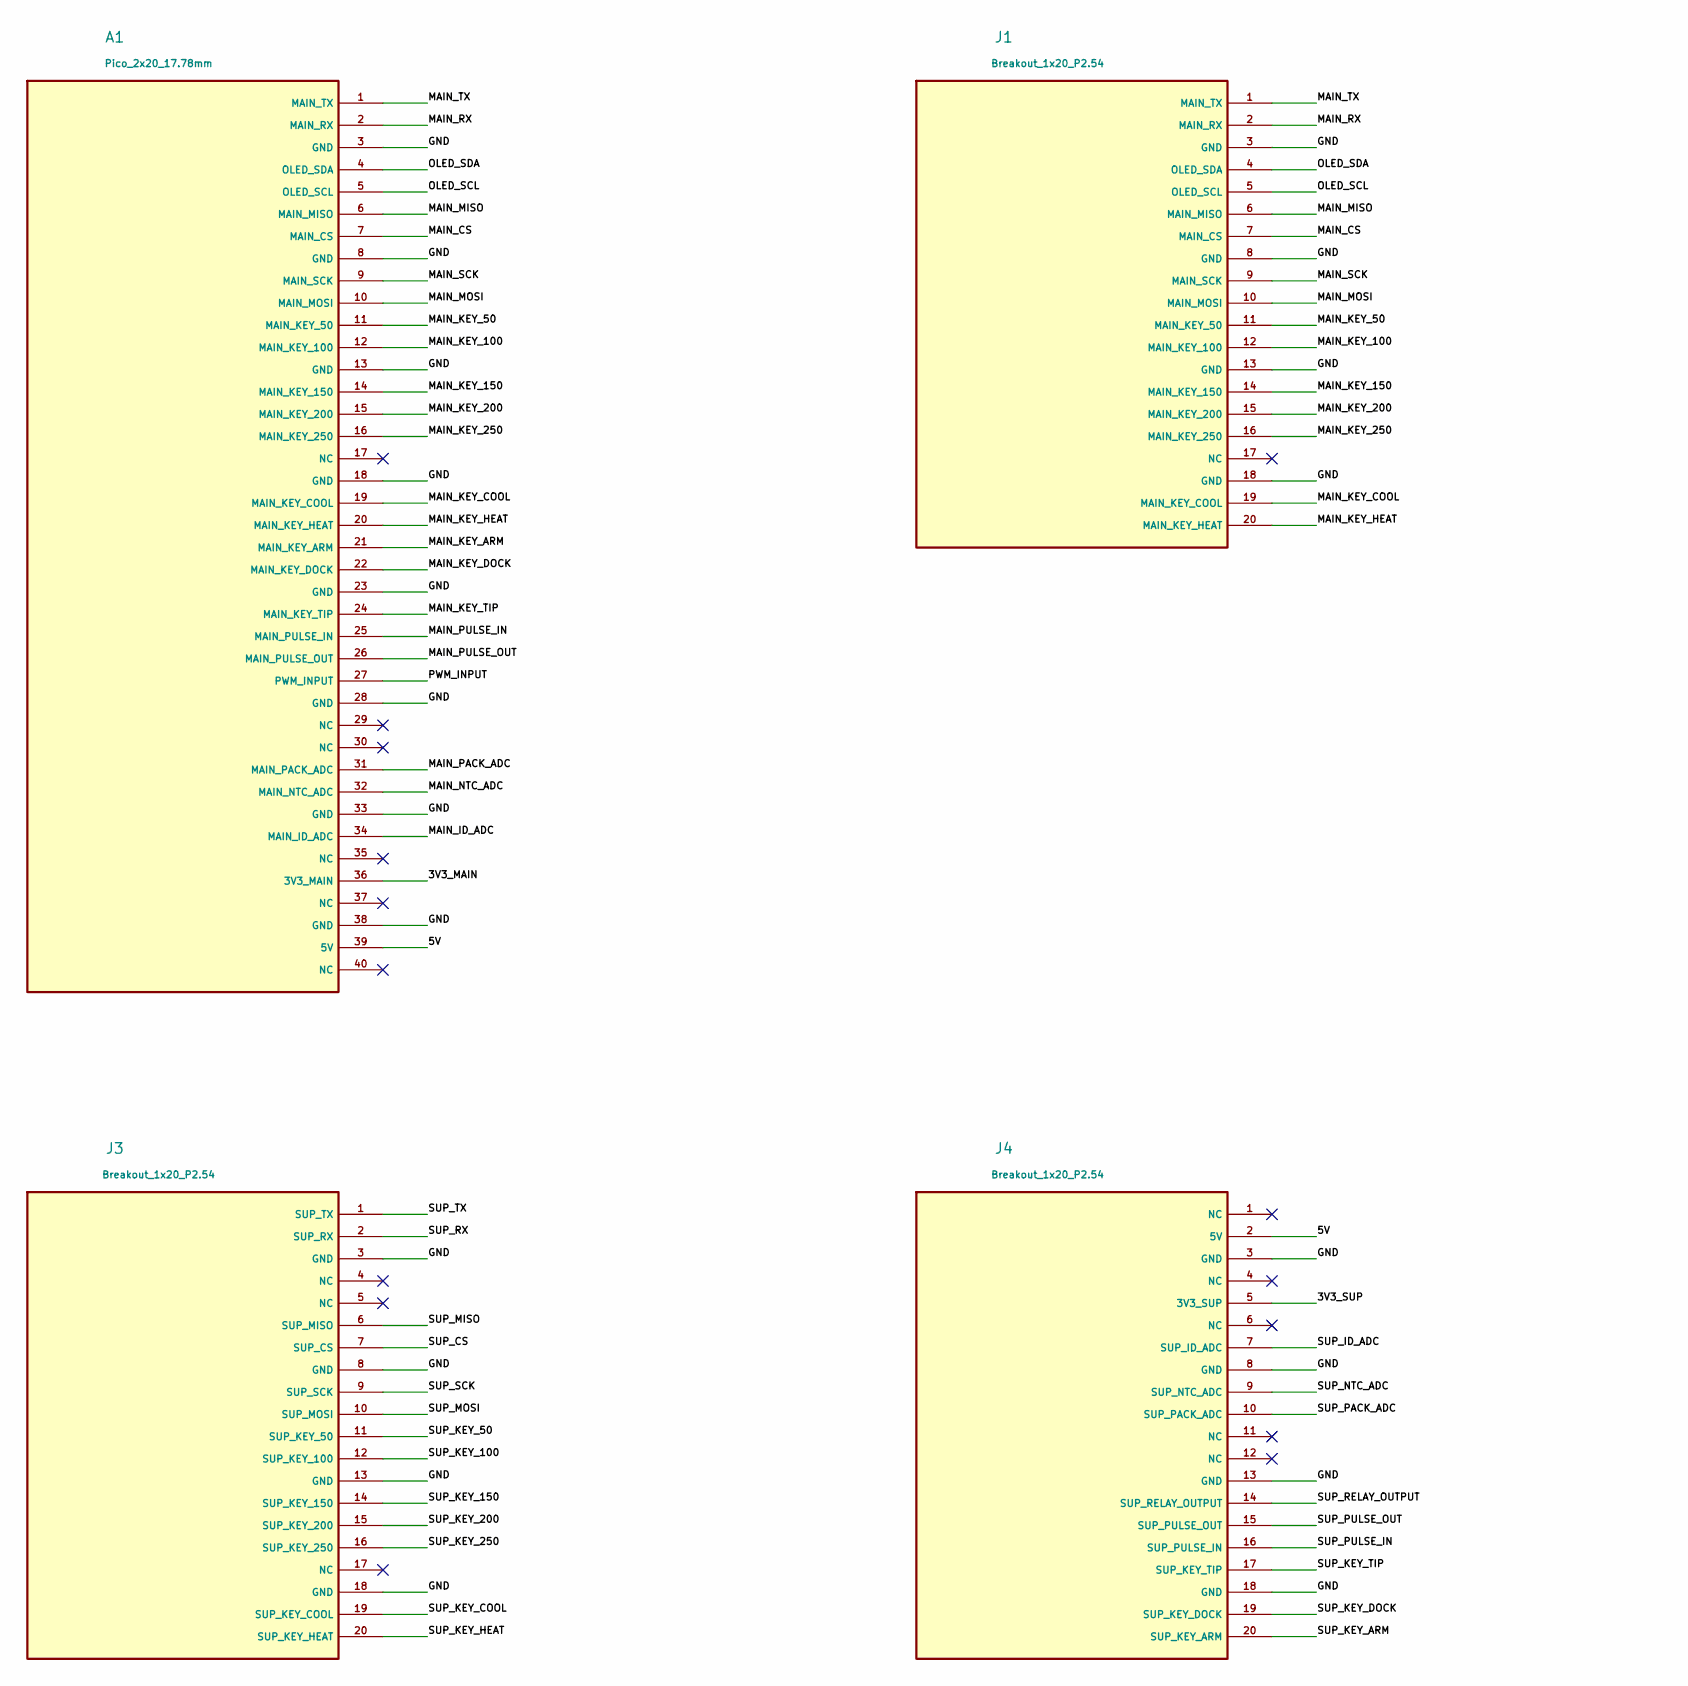
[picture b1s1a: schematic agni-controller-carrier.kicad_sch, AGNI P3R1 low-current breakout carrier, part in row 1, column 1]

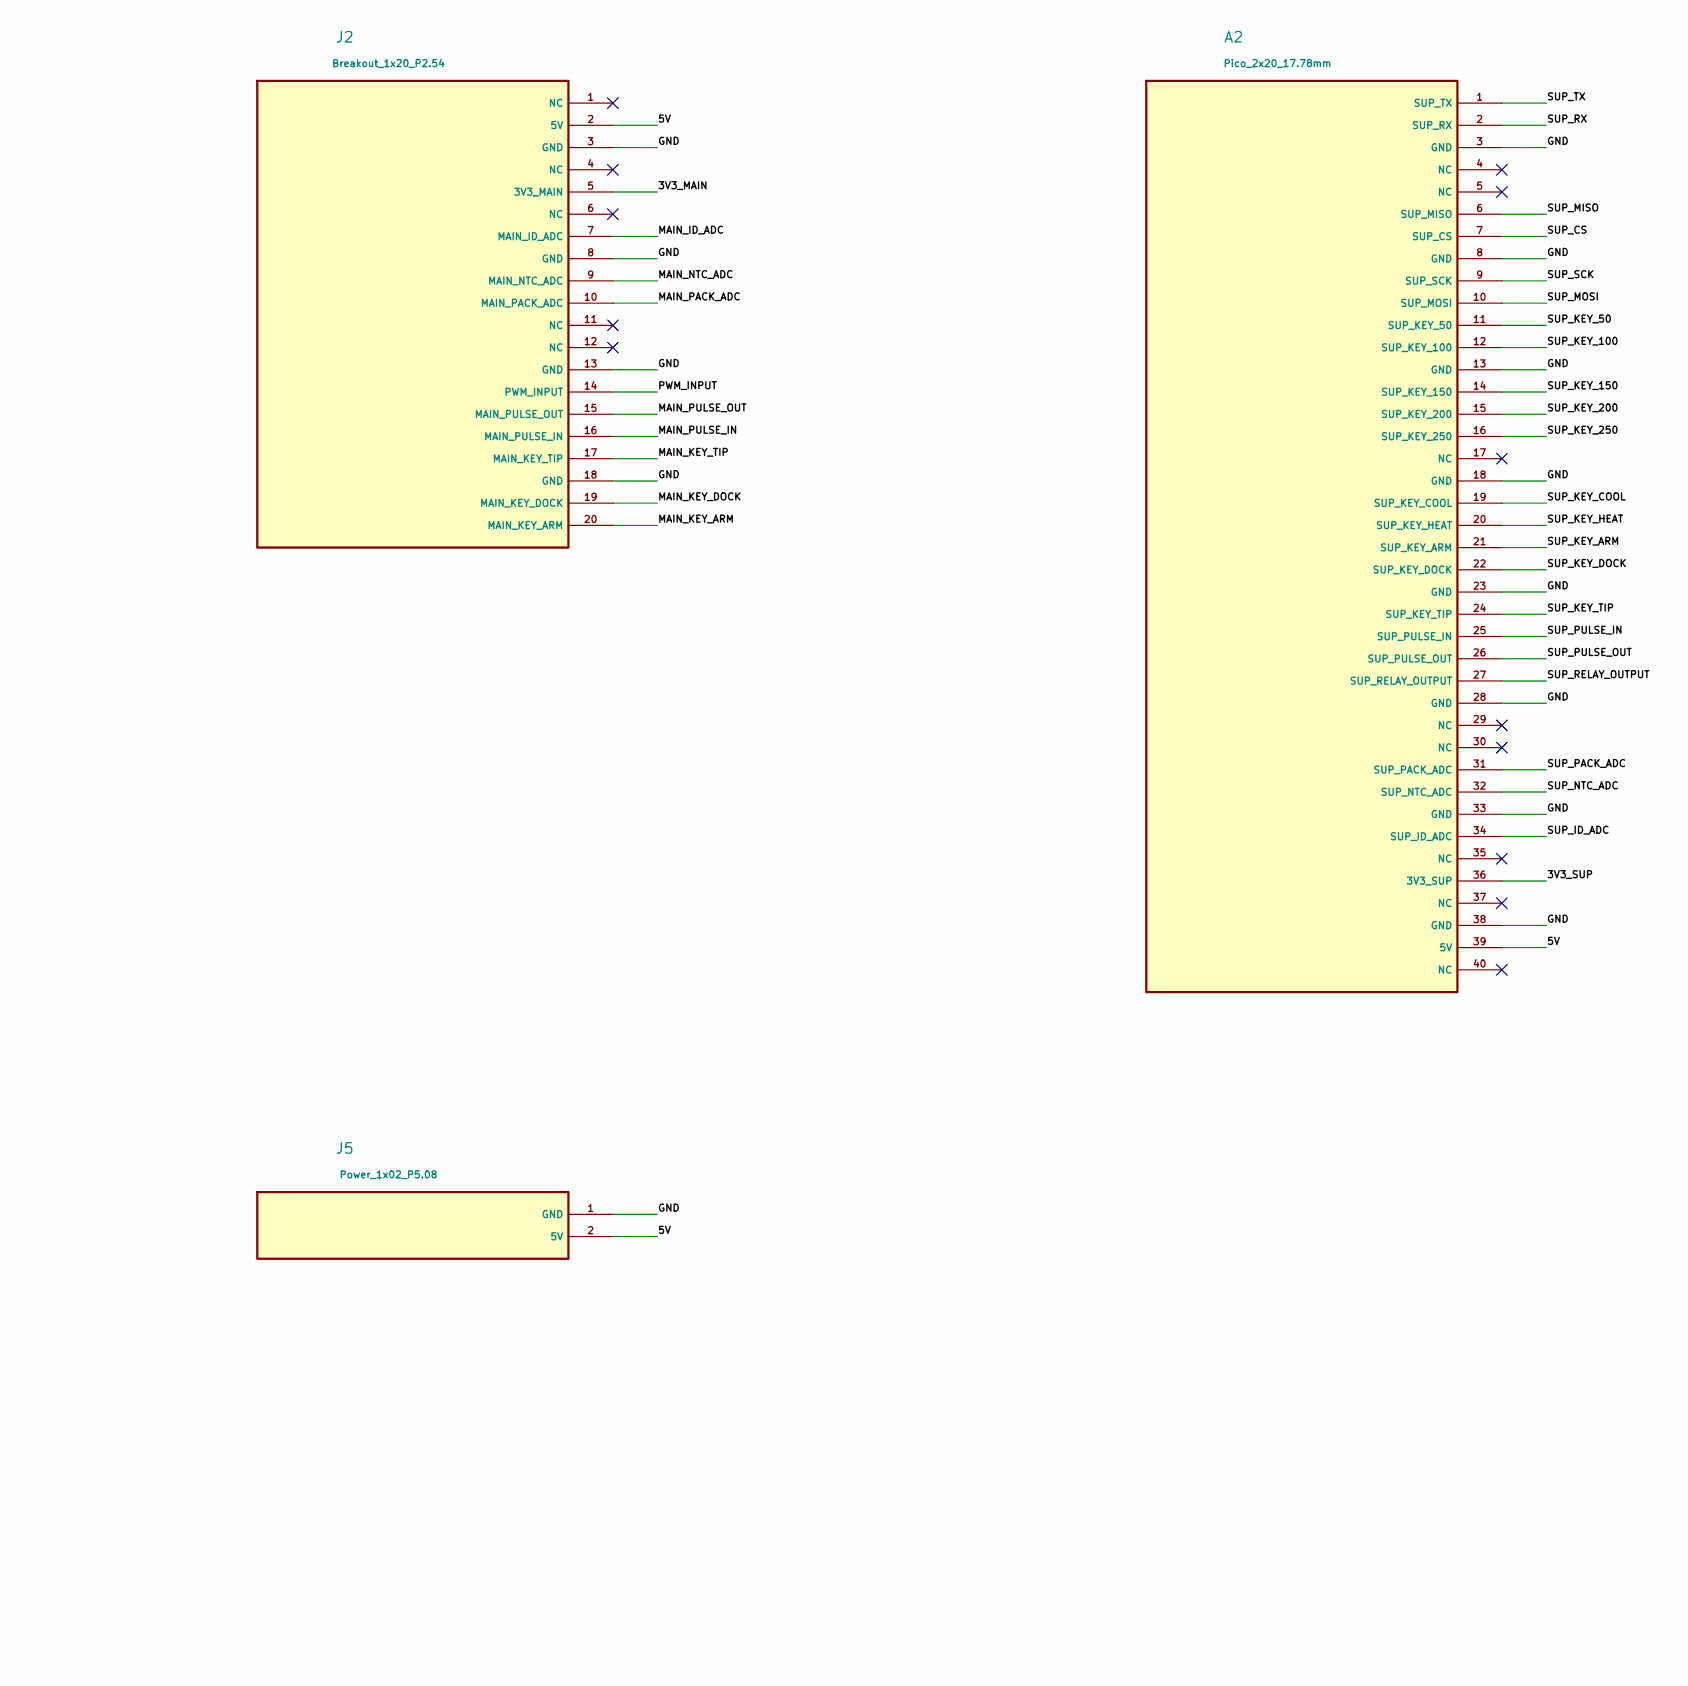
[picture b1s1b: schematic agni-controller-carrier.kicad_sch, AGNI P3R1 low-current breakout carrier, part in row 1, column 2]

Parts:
A1, A2: Pico_2x20_17.78mm
J1, J2, J3, J4: Breakout_1x20_P2.54
J5: Power_1x02_P5.08

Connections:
/3V3_MAIN: A1.36 (3V3_MAIN), J2.5 (3V3_MAIN)
/3V3_SUP: A2.36 (3V3_SUP), J4.5 (3V3_SUP)
/5V: A1.39 (5V), A2.39 (5V), J2.2 (5V), J4.2 (5V), J5.2 (5V)
/GND: A1.3 (GND), A1.8 (GND), A1.13 (GND), A1.18 (GND), A1.23 (GND), A1.28 (GND), A1.33 (GND), A1.38 (GND), A2.3 (GND), A2.8 (GND), A2.13 (GND), A2.18 (GND), A2.23 (GND), A2.28 (GND), A2.33 (GND), A2.38 (GND), J1.3 (GND), J1.8 (GND), J1.13 (GND), J1.18 (GND), J2.3 (GND), J2.8 (GND), J2.13 (GND), J2.18 (GND), J3.3 (GND), J3.8 (GND), J3.13 (GND), J3.18 (GND), J4.3 (GND), J4.8 (GND), J4.13 (GND), J4.18 (GND), J5.1 (GND)
/MAIN_CS: A1.7 (MAIN_CS), J1.7 (MAIN_CS)
/MAIN_ID_ADC: A1.34 (MAIN_ID_ADC), J2.7 (MAIN_ID_ADC)
/MAIN_KEY_50: A1.11 (MAIN_KEY_50), J1.11 (MAIN_KEY_50)
/MAIN_KEY_100: A1.12 (MAIN_KEY_100), J1.12 (MAIN_KEY_100)
/MAIN_KEY_150: A1.14 (MAIN_KEY_150), J1.14 (MAIN_KEY_150)
/MAIN_KEY_200: A1.15 (MAIN_KEY_200), J1.15 (MAIN_KEY_200)
/MAIN_KEY_250: A1.16 (MAIN_KEY_250), J1.16 (MAIN_KEY_250)
/MAIN_KEY_ARM: A1.21 (MAIN_KEY_ARM), J2.20 (MAIN_KEY_ARM)
/MAIN_KEY_COOL: A1.19 (MAIN_KEY_COOL), J1.19 (MAIN_KEY_COOL)
/MAIN_KEY_DOCK: A1.22 (MAIN_KEY_DOCK), J2.19 (MAIN_KEY_DOCK)
/MAIN_KEY_HEAT: A1.20 (MAIN_KEY_HEAT), J1.20 (MAIN_KEY_HEAT)
/MAIN_KEY_TIP: A1.24 (MAIN_KEY_TIP), J2.17 (MAIN_KEY_TIP)
/MAIN_MISO: A1.6 (MAIN_MISO), J1.6 (MAIN_MISO)
/MAIN_MOSI: A1.10 (MAIN_MOSI), J1.10 (MAIN_MOSI)
/MAIN_NTC_ADC: A1.32 (MAIN_NTC_ADC), J2.9 (MAIN_NTC_ADC)
/MAIN_PACK_ADC: A1.31 (MAIN_PACK_ADC), J2.10 (MAIN_PACK_ADC)
/MAIN_PULSE_IN: A1.25 (MAIN_PULSE_IN), J2.16 (MAIN_PULSE_IN)
/MAIN_PULSE_OUT: A1.26 (MAIN_PULSE_OUT), J2.15 (MAIN_PULSE_OUT)
/MAIN_RX: A1.2 (MAIN_RX), J1.2 (MAIN_RX)
/MAIN_SCK: A1.9 (MAIN_SCK), J1.9 (MAIN_SCK)
/MAIN_TX: A1.1 (MAIN_TX), J1.1 (MAIN_TX)
/OLED_SCL: A1.5 (OLED_SCL), J1.5 (OLED_SCL)
/OLED_SDA: A1.4 (OLED_SDA), J1.4 (OLED_SDA)
/PWM_INPUT: A1.27 (PWM_INPUT), J2.14 (PWM_INPUT)
/SUP_CS: A2.7 (SUP_CS), J3.7 (SUP_CS)
/SUP_ID_ADC: A2.34 (SUP_ID_ADC), J4.7 (SUP_ID_ADC)
/SUP_KEY_50: A2.11 (SUP_KEY_50), J3.11 (SUP_KEY_50)
/SUP_KEY_100: A2.12 (SUP_KEY_100), J3.12 (SUP_KEY_100)
/SUP_KEY_150: A2.14 (SUP_KEY_150), J3.14 (SUP_KEY_150)
/SUP_KEY_200: A2.15 (SUP_KEY_200), J3.15 (SUP_KEY_200)
/SUP_KEY_250: A2.16 (SUP_KEY_250), J3.16 (SUP_KEY_250)
/SUP_KEY_ARM: A2.21 (SUP_KEY_ARM), J4.20 (SUP_KEY_ARM)
/SUP_KEY_COOL: A2.19 (SUP_KEY_COOL), J3.19 (SUP_KEY_COOL)
/SUP_KEY_DOCK: A2.22 (SUP_KEY_DOCK), J4.19 (SUP_KEY_DOCK)
/SUP_KEY_HEAT: A2.20 (SUP_KEY_HEAT), J3.20 (SUP_KEY_HEAT)
/SUP_KEY_TIP: A2.24 (SUP_KEY_TIP), J4.17 (SUP_KEY_TIP)
/SUP_MISO: A2.6 (SUP_MISO), J3.6 (SUP_MISO)
/SUP_MOSI: A2.10 (SUP_MOSI), J3.10 (SUP_MOSI)
/SUP_NTC_ADC: A2.32 (SUP_NTC_ADC), J4.9 (SUP_NTC_ADC)
/SUP_PACK_ADC: A2.31 (SUP_PACK_ADC), J4.10 (SUP_PACK_ADC)
/SUP_PULSE_IN: A2.25 (SUP_PULSE_IN), J4.16 (SUP_PULSE_IN)
/SUP_PULSE_OUT: A2.26 (SUP_PULSE_OUT), J4.15 (SUP_PULSE_OUT)
/SUP_RELAY_OUTPUT: A2.27 (SUP_RELAY_OUTPUT), J4.14 (SUP_RELAY_OUTPUT)
/SUP_RX: A2.2 (SUP_RX), J3.2 (SUP_RX)
/SUP_SCK: A2.9 (SUP_SCK), J3.9 (SUP_SCK)
/SUP_TX: A2.1 (SUP_TX), J3.1 (SUP_TX)

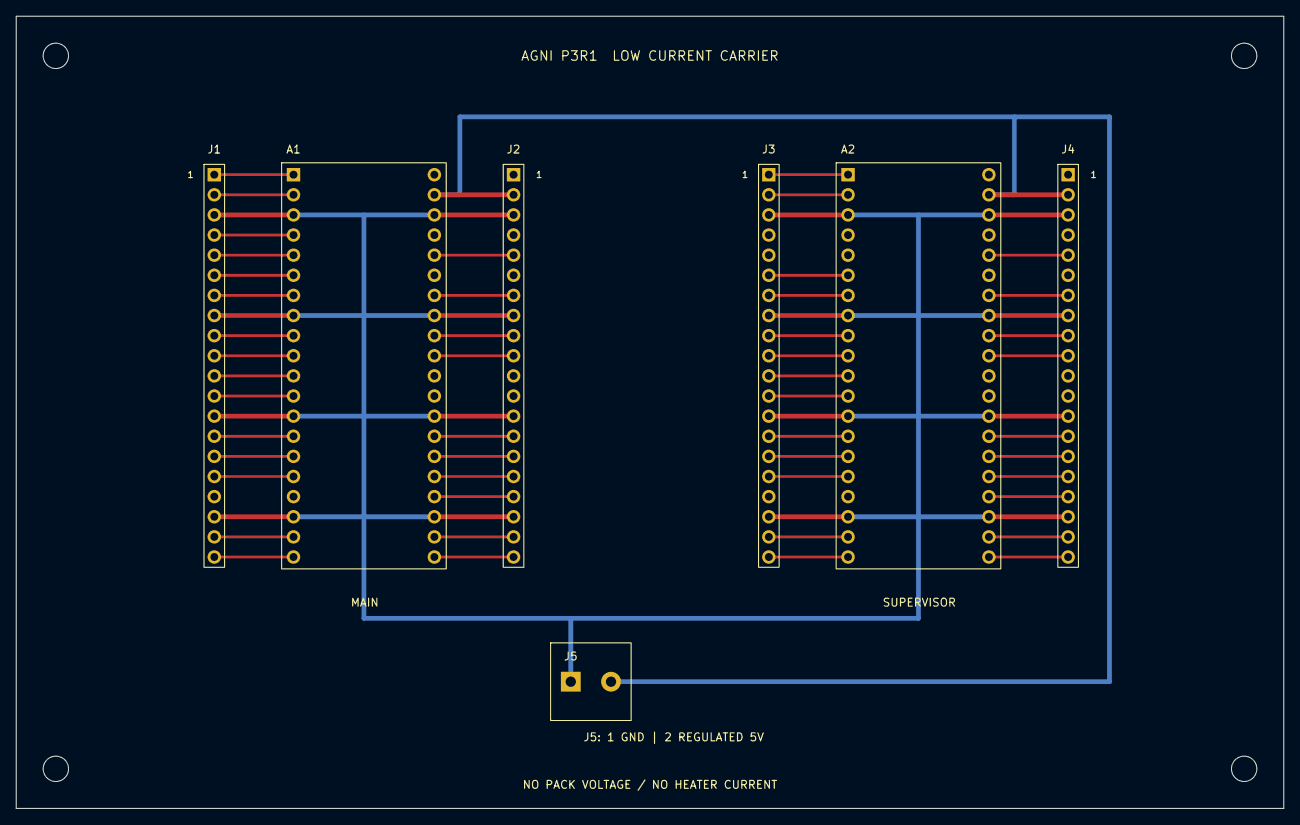
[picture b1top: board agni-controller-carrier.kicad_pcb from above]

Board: 2 copper layers, 160.0 x 100.0 mm, 11 parts (0 on the bottom side), 50 nets.

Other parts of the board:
H1, H2, H3, H4: MountingHole_3.2mm

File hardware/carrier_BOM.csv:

Reference,Quantity,Specification,Use_or_review
PCB_CARRIER,1,"AGNI P3R1; 160 x 100 mm; 2-layer FR4; nominal 1.6 mm; 35 um copper; mask both sides; top silkscreen","Fabrication candidate only; independent CAM and physical footprint review before order"
A1/A2 sockets,4,"1x20 female socket strip; 2.54 mm pitch; 0.64 mm square-pin compatible; straight through-hole; 1.0 mm PCB drill","Two strips per Pico; choose matched stack height; verify orientation and engagement"
J1/J2/J3/J4,4,"1x20 straight male header; 2.54 mm pitch; 0.64 mm square posts; 1.0 mm drill","Low-current external breakouts; external 1k branches and all other circuits still required"
J5,1,"Phoenix Contact 1715721 MKDS 1.5/2-5.08; 2-position; 5.08 mm pitch; 1.3 mm drill","Pin 1 GND; pin 2 regulated 5 V only; confirm actual footprint and torque against current supplier drawing"
Carrier screws,4,"M3 x 6 pan head; insulating washers as needed","Fit model pilot posts; check protrusion and engagement"
Lid screws,4,"M3 x 10 pan head","Fit model pilot posts; qualify repeated use"
Clamp screws,2,"M3 x 10 pan head with washers","Check cable retention; insulating grommet required"

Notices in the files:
README.md:
Do not describe public hosting alone as an open-source license grant.
